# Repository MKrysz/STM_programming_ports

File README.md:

# STM32 Programming Port

## About

<!-- While making project using STM32 MCUs I always find it infuriating that I lose so much time and effort on something so mundane as  -->
The goal of this project is to convert ports found in those cheap ST-Link programmers to other useful ports like, standard 20-pin ARM JTAG connector or typical 4-pin Single Wire connector commonly found in chinese STM32-based development boards. As additional features I added a reset button and power jumper.

## Schematic

## PCB

### Before assembly

### After assembly

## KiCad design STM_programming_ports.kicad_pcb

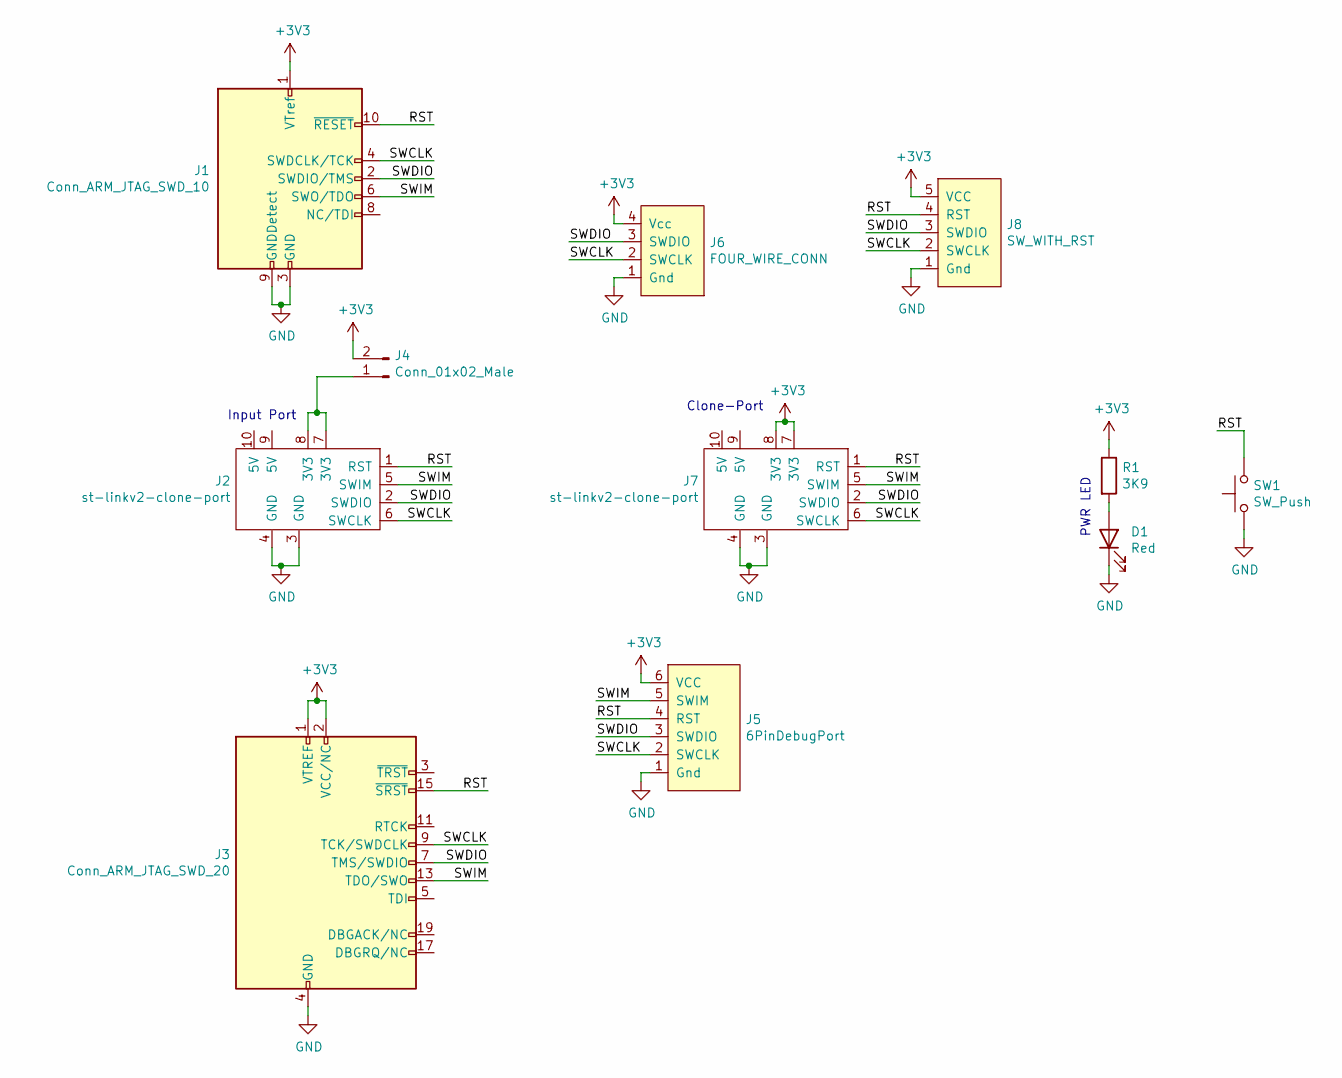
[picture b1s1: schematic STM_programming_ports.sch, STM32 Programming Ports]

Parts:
D1: Red; LED_1206_3216Metric_Pad1.42x1.75mm_HandSolder
J1: Conn_ARM_JTAG_SWD_10; IDC-Header_2x05_P2.54mm_Vertical
J2: st-linkv2-clone-port; IDC-Header_2x05_P2.54mm_Horizontal
J3: Conn_ARM_JTAG_SWD_20; IDC-Header_2x10_P2.54mm_Vertical
J4: Conn_01x02_Male; PinHeader_1x02_P2.54mm_Vertical
J5: 6PinDebugPort; IDC-Header_2x03_P2.54mm_Vertical
J6: FOUR_WIRE_CONN; PinHeader_1x04_P2.54mm_Vertical
J7: st-linkv2-clone-port; IDC-Header_2x05_P2.54mm_Vertical
J8: SW_WITH_RST; PinHeader_1x05_P2.54mm_Vertical
R1: 3K9; R_1206_3216Metric_Pad1.30x1.75mm_HandSolder
SW1: SW_Push; TSB008

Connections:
+3V3: J1.1 (VTref), J3.1 (VTREF), J3.2 (VCC/NC), J4.2, J5.6 (VCC), J6.4 (Vcc), J7.7 (3V3), J7.8 (3V3), J8.5 (VCC), R1.1
/RST: J1.10 (~RESET~), J2.1 (RST), J3.15 (~SRST~), J5.4 (RST), J7.1 (RST), J8.4 (RST), SW1.2
/SWCLK: J1.4 (SWDCLK/TCK), J2.6 (SWCLK), J3.9 (TCK/SWDCLK), J5.2 (SWCLK), J6.2 (SWCLK), J7.6 (SWCLK), J8.2 (SWCLK)
/SWDIO: J1.2 (SWDIO/TMS), J2.2 (SWDIO), J3.7 (TMS/SWDIO), J5.3 (SWDIO), J6.3 (SWDIO), J7.2 (SWDIO), J8.3 (SWDIO)
/SWIM: J1.6 (SWO/TDO), J2.5 (SWIM), J3.13 (TDO/SWO), J5.5 (SWIM), J7.5 (SWIM)
GND: D1.1 (K), J1.3 (GND), J1.5 (GND), J1.9 (GNDDetect), J2.3 (GND), J2.4 (GND), J3.4 (GND), J3.6 (GND), J3.8 (GND), J3.10 (GND), J3.12 (GND), J3.14 (GND), J3.16 (GND), J3.18 (GND), J3.20 (GND), J5.1 (Gnd), J6.1 (Gnd), J7.3 (GND), J7.4 (GND), J8.1 (Gnd), SW1.1
unnamed: D1.2 (A), R1.2
unnamed: J2.7 (3V3), J2.8 (3V3), J4.1

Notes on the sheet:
PWR LED
Input Port
Clone-Port

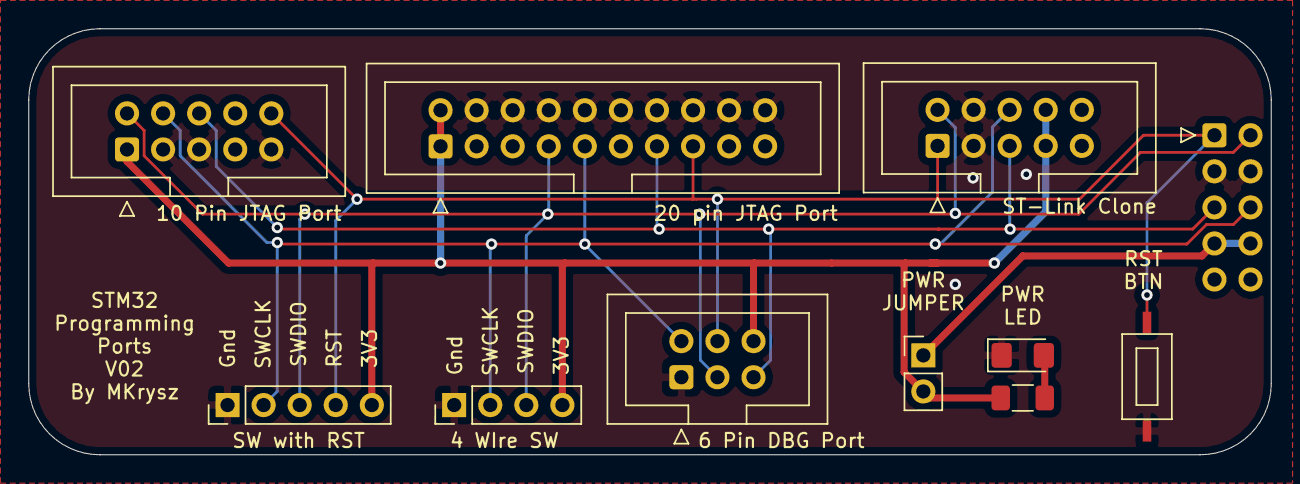
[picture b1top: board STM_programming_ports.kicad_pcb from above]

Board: 2 copper layers, 87.5 x 30.0 mm, 11 parts (0 on the bottom side), 8 nets.

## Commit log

2022-05-13 Version01
2022-05-13 Version02
2022-05-27 Minor position changes
2022-05-27 Generated PCB's Gerbers
2022-07-18 Written README
